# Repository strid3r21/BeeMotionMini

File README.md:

# Bee Motion Mini

## **Buy on** [Tindie](https://www.tindie.com/products/smartbee/bee-motion-mini-esp32-pir)

## **Visit our** [Discord](https://tinyurl.com/Bee-Motion-Discord-Git)

# Programming on Arduino

## Add the Espressif ESP32 arduino board library to Arduino IDE
File > Preferences > at the bottom "Additional Board Manager URLS" paste in this url
https://raw.githubusercontent.com/espressif/arduino-esp32/gh-pages/package_esp32_index.json 
 
From there you will be able to search and add the ESP32 board library from the board library search bar. install the ESP32 library by Espressif and make sure you're using version number 2.0.5 or later. You will then be able to select your Bee Motion Mini from the board manager.

## How to program the Bee Motion
In order to program the Bee Motion you need to put it into download mode. To do so all you need to do is connect the USB-C cable and then press and hold the boot button. with the boot button being held down, press the reset button and release. then you can release the boot button. this will put the Bee Motion into download mode which will allow it to be programmed. Then for the board, select "Bee Motion Mini" from the board manager.

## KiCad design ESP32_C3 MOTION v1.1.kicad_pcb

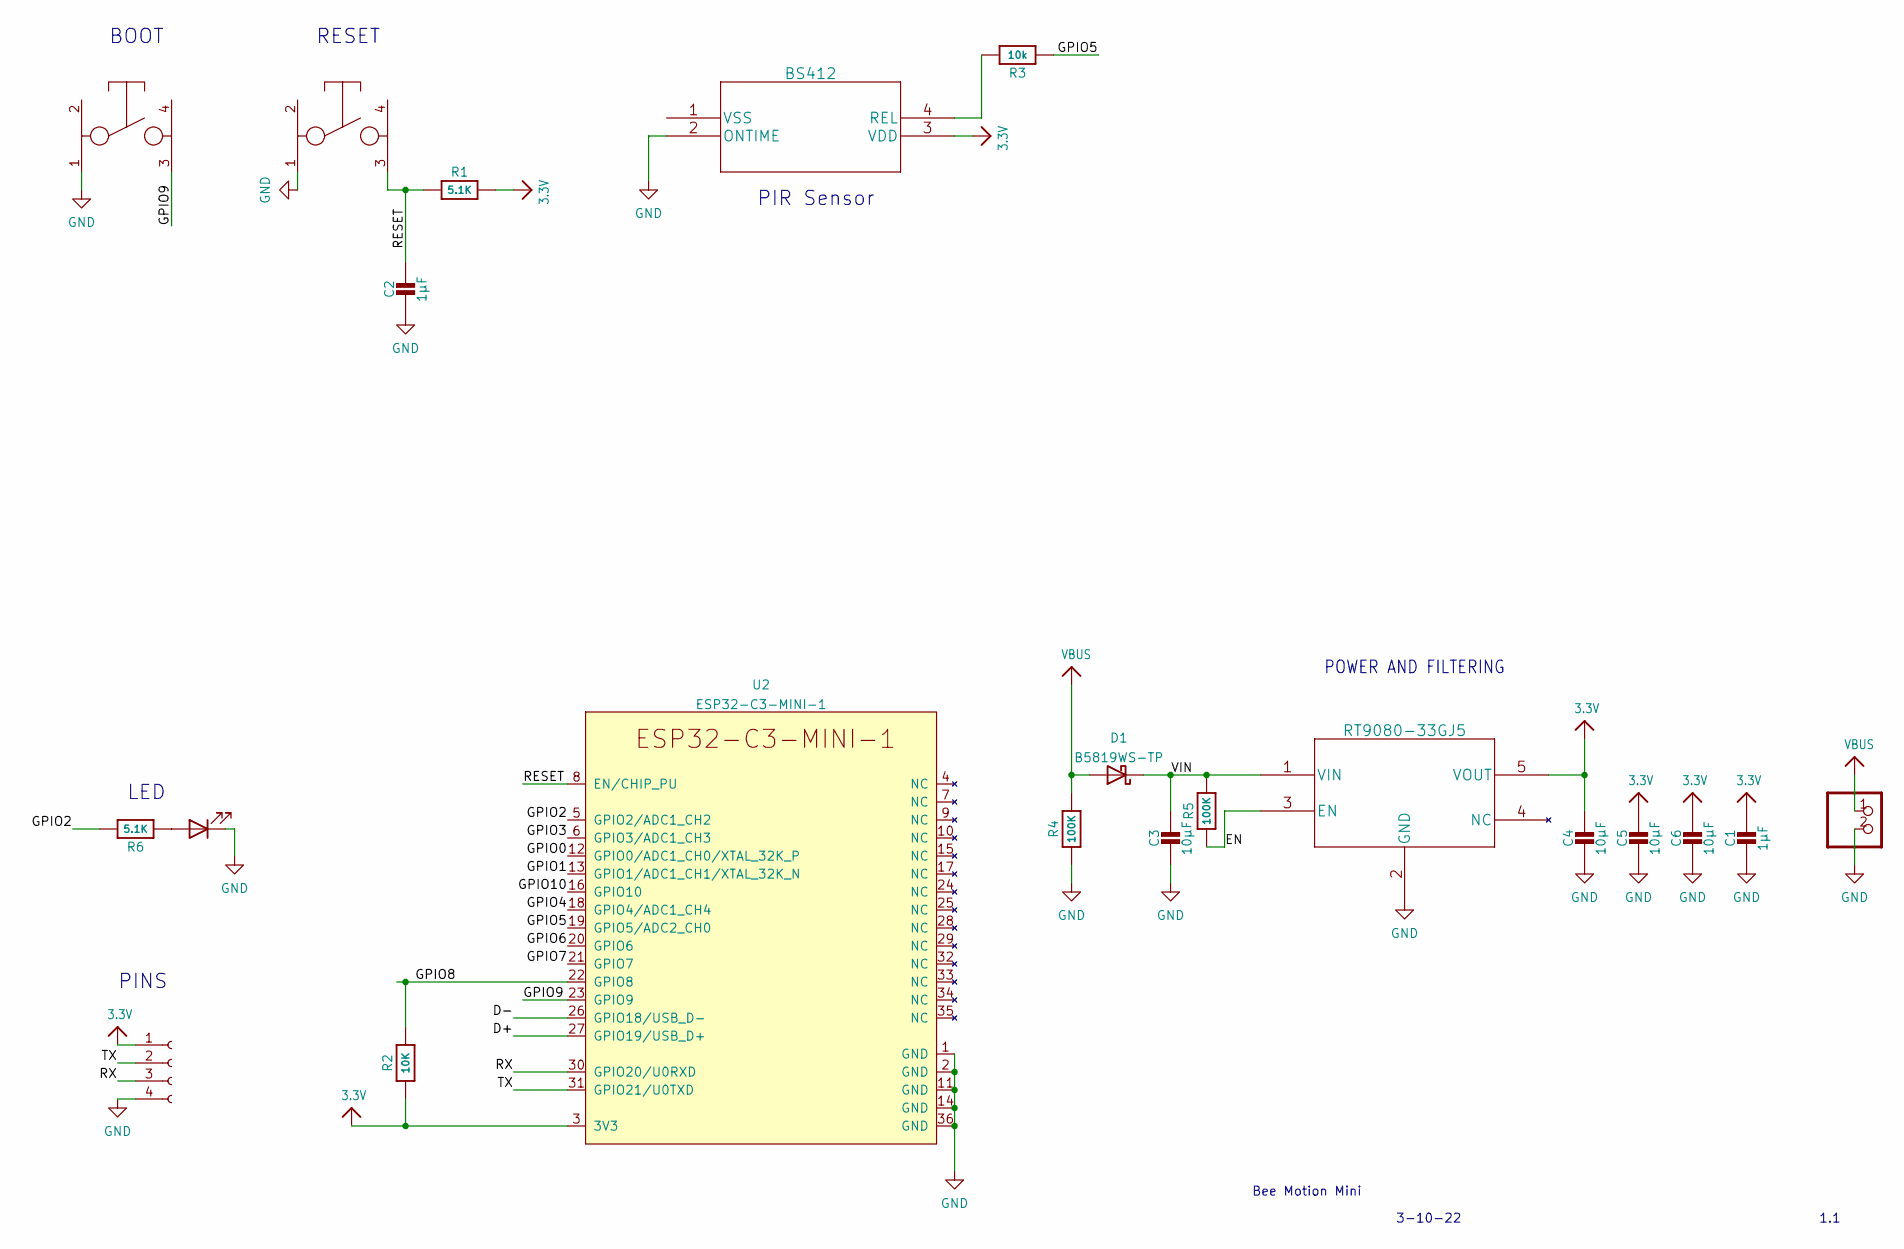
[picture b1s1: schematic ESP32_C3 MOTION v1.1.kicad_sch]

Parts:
C1, C2: 1µF; C_0603_1608Metric
C3, C4, C5, C6: 10µF; C_0603_1608Metric
D1: B5819WS-TP; D_SOD-323
D2: LED; LED_0603_1608Metric
J1: Conn_01x04_Female; PinHeader_1x04_P2.54mm_Vertical
R1, R6: 5.1K; R_0603_1608Metric
R2: 10K; R_0603_1608Metric
R3: 10k; R_0603_1608Metric
R4, R5: 100K; R_0603_1608Metric
SW1, SW2: TSA343g00-250DZ; TSA343G0 BTN
U1: BS412
U2: ESP32-C3-MINI-1
U3: RT9080-33GJ5
X1: JSTPH; JST_PH_S2B-PH-SM4-TB_1x02-1MP_P2.00mm_Horizontal

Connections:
3.3V: C1.1, C4.1, C5.1, C6.1, J1.1, R1.2, R2.1, U1.3 (VDD), U2.3 (3V3), U3.5 (VOUT)
/D+: U2.27 (GPIO19/USB_D+)
/D-: U2.26 (GPIO18/USB_D-)
/EN: R5.1, U3.3 (EN)
/GPIO0: U2.12 (GPIO0/ADC1_CH0/XTAL_32K_P)
/GPIO1: U2.13 (GPIO1/ADC1_CH1/XTAL_32K_N)
/GPIO2: R6.2, U2.5 (GPIO2/ADC1_CH2)
/GPIO3: U2.6 (GPIO3/ADC1_CH3)
/GPIO4: U2.18 (GPIO4/ADC1_CH4)
/GPIO5: R3.1, U2.19 (GPIO5/ADC2_CH0)
/GPIO6: U2.20 (GPIO6)
/GPIO7: U2.21 (GPIO7)
/GPIO8: R2.2, U2.22 (GPIO8)
/GPIO9: SW2.3 (K), U2.23 (GPIO9)
/GPIO10: U2.16 (GPIO10)
/RESET: C2.1, R1.1, SW1.3 (K), U2.8 (EN/CHIP_PU)
/RX: J1.3, U2.30 (GPIO20/U0RXD)
/TX: J1.2, U2.31 (GPIO21/U0TXD)
/VIN: C3.1, D1.1 (K), R5.2, U3.1 (VIN)
GND: C1.2, C2.2, C3.2, C4.2, C5.2, C6.2, D2.1 (K), J1.4, R4.1, SW1.1, SW2.1, U1.2 (ONTIME), U2.1 (GND), U2.2 (GND), U2.11 (GND), U2.14 (GND), U2.36 (GND), U3.2 (GND), X1.2
unnamed: D2.2 (A), R6.1
unnamed: R3.2, U1.4 (REL)
VBUS: D1.2 (A), R4.2, X1.1

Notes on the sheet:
Bee Motion Mini
PINS
POWER AND FILTERING
3-10-22
LED
1.1
PIR Sensor
BOOT
RESET

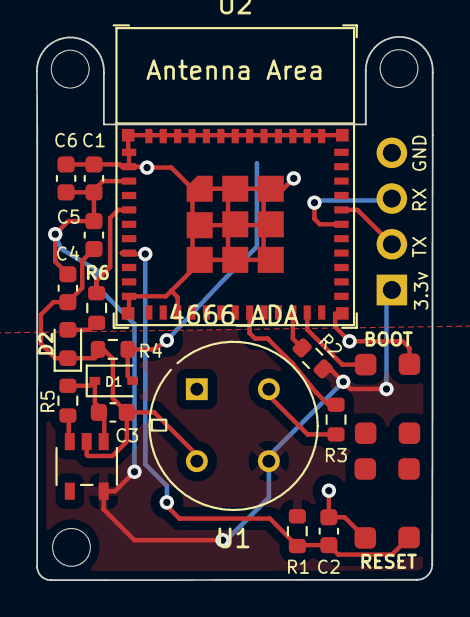
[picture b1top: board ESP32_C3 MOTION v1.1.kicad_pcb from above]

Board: 2 copper layers, 22.0 x 30.2 mm, 21 parts (1 on the bottom side), 14 nets.

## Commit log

2022-03-29 added example code for the bee motion mini
2022-04-05 added Schematics and step file
2022-04-06 organized the files
2022-04-06 added info card
2022-05-11 added a MQTT example with deep sleep
    this sketch uses the adafruits free MQTT service.
2022-05-13 added video on how to program the bee motion mini
2022-05-14 added discord link
2022-05-14 Added Tindie link

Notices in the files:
parts and their libraries:
Copyright 2021 Accelerated Designs. All rights reserved.
